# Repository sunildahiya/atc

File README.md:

### Automatic Toilet Cleaner
This repository contains Solidwork design, Navigation Code and IP code for InterIIT Automatic Toilet Cleaner Competition.

#### Minimal HSV Channels for detecting different Color

 1. White    -   Saturation from 0 to someValue
 2. Green    -   Using 1, hue 0 to someValue
 3. Blue     -   saturation from somevalue to 255
 4. Red      -   Using 3, hue from somevalue to 255

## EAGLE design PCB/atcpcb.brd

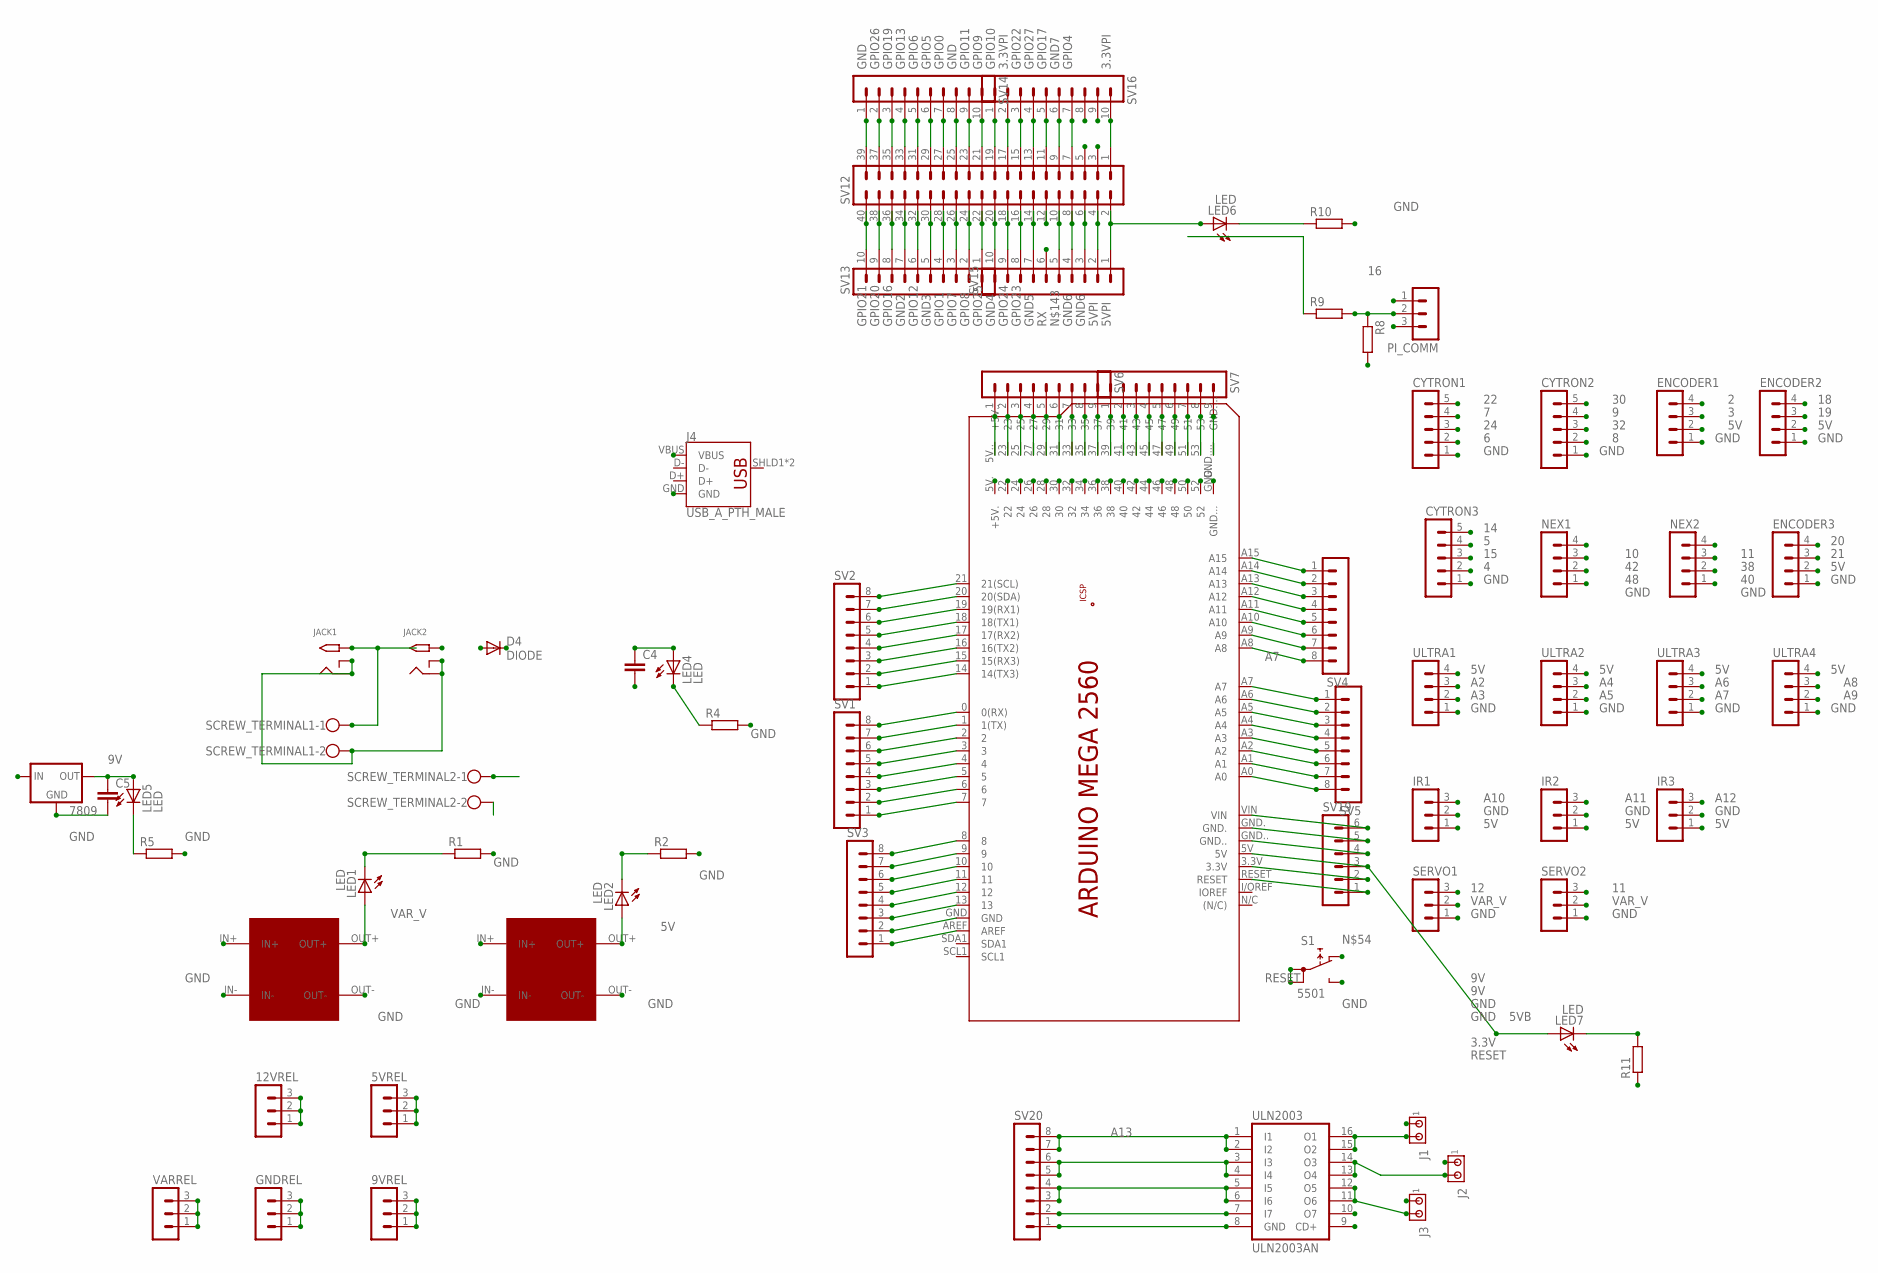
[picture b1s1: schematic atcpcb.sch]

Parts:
5VREL, 9VREL, 12VREL: RELIMATE_03-1; MA03-1
7809: VOLTAGE_REGULATOR_78XXS; 78XXS
C4, C5: CAPACITOR075-063X106; C075-063X106
CYTRON1, CYTRON2, CYTRON3: RELIMATE_05-1; MA05-1
D4: DIODE
ENCODER1, ENCODER2, ENCODER3: RELIMATE_04-1; MA04-1
GNDREL: RELIMATE_03-1; MA03-1
IR1, IR2, IR3: RELIMATE_03-1; MA03-1
J1, J2, J3: MTA02-100; 10X02MTA
J4: USB_A_PTH_MALE; USB-A-H
JACK1, JACK2: 2.1MM_POWER_JACKTHM; POWER_JACK
LED1, LED2, LED4, LED5, LED6, LED7: LED; LED3MM
NEX1, NEX2: RELIMATE_04-1; MA04-1
PCB1: ARDUINO_MEGA2560
PI_COMM: RELIMATE_03-1; MA03-1
R1, R2, R4, R5, R8, R9, R10, R11: RESISTANCE0207/10; 0207/10
S1: 5501
SCREW_TERMINAL1, SCREW_TERMINAL2: SCREW_TERMINAL_POWER; POWER_CONNECTOR
SERVO1, SERVO2: RELIMATE_03-1; MA03-1
SV1, SV2, SV3, SV4, SV5, SV20: RELIMATE_08-1; MA08-1
SV6, SV7: RELIMATE_09-1; MA09-1
SV12: RELIMATE_20-2; MA20-2
SV13, SV14, SV15, SV16: RELIMATE_10-1; MA10-1
SV19: RELIMATE_06-1; MA06-1
U$1, U$2: BUCK_CONVERTER; MPN LNK304DN
ULN2003: ULN2003AN; DIL16
ULTRA1, ULTRA2, ULTRA3, ULTRA4: RELIMATE_04-1; MA04-1
VARREL: RELIMATE_03-1; MA03-1

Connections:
0: PCB1.0 (0(RX)), SV1.8
1: PCB1.1 (1(TX)), SV1.7
2: ENCODER1.4, PCB1.2, SV1.6
3: ENCODER1.3, PCB1.3, SV1.5
3.3V: PCB1.3.3V, SV19.2
3.3VPI: SV12.1, SV12.17, SV16.2, SV16.10
4: CYTRON3.2, PCB1.4, SV1.4
5: CYTRON3.4, PCB1.5, SV1.3
5V: 5VREL.1, 5VREL.2, 5VREL.3, ENCODER1.2, ENCODER2.2, ENCODER3.2, IR1.1, IR2.1, IR3.1, J4.VBUS, LED2.A, U$2.OUT+, ULTRA1.4, ULTRA2.4, ULTRA3.4, ULTRA4.4
5VB: LED7.A, PCB1.5V, SV19.3
5VC: PCB1.5V. (+5V.), PCB1.5V.. (+5V..), SV6.1
5VPI: LED6.A, SV12.2, SV12.4, SV15.1, SV15.2
6: CYTRON1.2, PCB1.6, SV1.2
7: CYTRON1.4, PCB1.7, SV1.1
8: CYTRON2.2, PCB1.8, SV3.8
9: CYTRON2.4, PCB1.9, SV3.7
9V: 9VREL.1, 9VREL.2, 9VREL.3, 7809.OUT, C5.1, LED5.A, PCB1.VIN, SV19.6
10: NEX1.4, PCB1.10, SV3.6
11: NEX2.4, PCB1.11, SERVO2.3, SV3.5
12: PCB1.12, SERVO1.3, SV3.4
12V: 12VREL.1, 12VREL.2, 12VREL.3, 7809.IN, C4.1, D4.C, J1.1, J2.1, J3.1, LED4.A, U$1.IN+, U$2.IN+, ULN2003.9 (CD+)
13: PCB1.13, SV3.3
14: CYTRON3.5, PCB1.14 (14(TX3)), SV2.1
15: CYTRON3.3, PCB1.15 (15(RX3)), SV2.2
16: PCB1.16 (16(TX2)), PI_COMM.1, SV2.3
17: PCB1.17 (17(RX2)), PI_COMM.2, R8.1, R9.2, SV2.4
18: ENCODER2.4, PCB1.18 (18(TX1)), SV2.5
19: ENCODER2.3, PCB1.19 (19(RX1)), SV2.6
20: ENCODER3.4, PCB1.20 (20(SDA)), SV2.7
21: ENCODER3.3, PCB1.21 (21(SCL)), SV2.8
22: CYTRON1.5, PCB1.22
23: PCB1.23, SV6.2
24: CYTRON1.3, PCB1.24
25: PCB1.25, SV6.3
26: PCB1.26
27: PCB1.27, SV6.4
28: PCB1.28
29: PCB1.29, SV6.5
30: CYTRON2.5, PCB1.30
31: PCB1.31, SV6.6
32: CYTRON2.3, PCB1.32
33: PCB1.33, SV6.7
34: PCB1.34
35: PCB1.35, SV6.8
36: PCB1.36
37: PCB1.37, SV6.9
38: NEX2.3, PCB1.38
39: PCB1.39, SV7.1
40: NEX2.2, PCB1.40
41: PCB1.41, SV7.2
42: NEX1.3, PCB1.42
43: PCB1.43, SV7.3
44: PCB1.44
45: PCB1.45, SV7.4
46: PCB1.46
47: PCB1.47, SV7.5
48: NEX1.2, PCB1.48
49: PCB1.49, SV7.6
50: PCB1.50
51: PCB1.51, SV7.7
52: PCB1.52
53: PCB1.53, SV7.8
A0: PCB1.A0, SV5.8
A1: PCB1.A1, SV5.7
A2: PCB1.A2, SV5.6, ULTRA1.3
A3: PCB1.A3, SV5.5, ULTRA1.2
A4: PCB1.A4, SV5.4, ULTRA2.3
A5: PCB1.A5, SV5.3, ULTRA2.2
A6: PCB1.A6, SV5.2, ULTRA3.3
A7: PCB1.A7, SV5.1, ULTRA3.2
A8: PCB1.A8, SV4.8, ULTRA4.3
A9: PCB1.A9, SV4.7, ULTRA4.2
A10: IR1.3, PCB1.A10, SV4.6
A11: IR2.3, PCB1.A11, SV4.5
A12: IR3.3, PCB1.A12, SV4.4
A13: PCB1.A13, SV4.3, SV20.7, SV20.8, ULN2003.1 (I1), ULN2003.2 (I2)
A14: PCB1.A14, SV4.2, SV20.5, SV20.6, ULN2003.3 (I3), ULN2003.4 (I4)
A15: PCB1.A15, SV4.1, SV20.3, SV20.4, ULN2003.5 (I5), ULN2003.6 (I6)
AREF: PCB1.AREF, SV3.1
GND: 7809.GND, C4.2, C5.2, CYTRON1.1, CYTRON2.1, CYTRON3.1, ENCODER1.1, ENCODER2.1, ENCODER3.1, GNDREL.1, GNDREL.2, GNDREL.3, IR1.2, IR2.2, IR3.2, J4.GND, JACK1.RING, JACK1.RING_SW, JACK2.RING, JACK2.RING_SW, NEX1.1, NEX2.1, PCB1.GND, PCB1.GND., PCB1.GND.., PCB1.GND..., PCB1.GND...., PI_COMM.3, R1.2, R2.2, R4.2, R5.2, R8.2, R10.2, R11.1, S1.NO, SCREW_TERMINAL1.2, SCREW_TERMINAL2.2, SERVO1.1, SERVO2.1, SV3.2, SV7.9, SV12.25, SV12.39, SV14.1, SV14.8, SV19.4, SV19.5, SV20.1, U$1.IN-, U$1.OUT-, U$2.IN-, U$2.OUT-, ULN2003.8 (GND), ULTRA1.1, ULTRA2.1, ULTRA3.1, ULTRA4.1
GND2: SV12.34, SV13.7
GND3: SV12.30, SV13.5
GND4: SV12.20, SV15.10
GND5: SV12.14, SV15.7
GND6: SV12.6, SV12.8, SV15.3, SV15.4
GND7: SV12.9, SV16.6
GPIO0: SV12.27, SV14.7
GPIO1: SV12.28, SV13.4
GPIO4: SV12.7, SV16.7
GPIO5: SV12.29, SV14.6
GPIO6: SV12.31, SV14.5
GPIO7: SV12.26, SV13.3
GPIO8: SV12.24, SV13.2
GPIO9: SV12.21, SV14.10
GPIO10: SV12.19, SV16.1
GPIO11: SV12.23, SV14.9
GPIO12: SV12.32, SV13.6
GPIO13: SV12.33, SV14.4
GPIO16: SV12.36, SV13.8
GPIO17: SV12.11, SV16.5
GPIO19: SV12.35, SV14.3
GPIO20: SV12.38, SV13.9
GPIO21: SV12.40, SV13.10
GPIO22: SV12.15, SV16.3
GPIO23: SV12.16, SV15.8
GPIO24: SV12.18, SV15.9
GPIO25: SV12.22, SV13.1
GPIO26: SV12.37, SV14.2
GPIO27: SV12.13, SV16.4
unnamed: LED1.K (C), R1.1
unnamed: LED2.K (C), R2.1
unnamed: LED6.K (C), R10.1
unnamed: LED7.K (C), R11.2
unnamed: SV20.2, ULN2003.7 (I7)
unnamed: J1.2, ULN2003.15 (O2), ULN2003.16 (O1)
unnamed: J2.2, ULN2003.13 (O4), ULN2003.14 (O3)
unnamed: J3.2, ULN2003.11 (O6), ULN2003.12 (O5)
unnamed: LED4.K (C), R4.1
unnamed: LED5.K (C), R5.1
unnamed: SV12.10, SV15.5
RESET: PCB1.RESET, S1.1A, S1.1B, SV19.1
RX: R9.1, SV12.12, SV15.6
SCL: SV12.5, SV16.8
SDA: SV12.3, SV16.9
VAR_V: LED1.A, SERVO1.2, SERVO2.2, U$1.OUT+, VARREL.1, VARREL.2, VARREL.3
VIN: D4.A, JACK1.TIP, JACK2.TIP, SCREW_TERMINAL1.1, SCREW_TERMINAL2.1

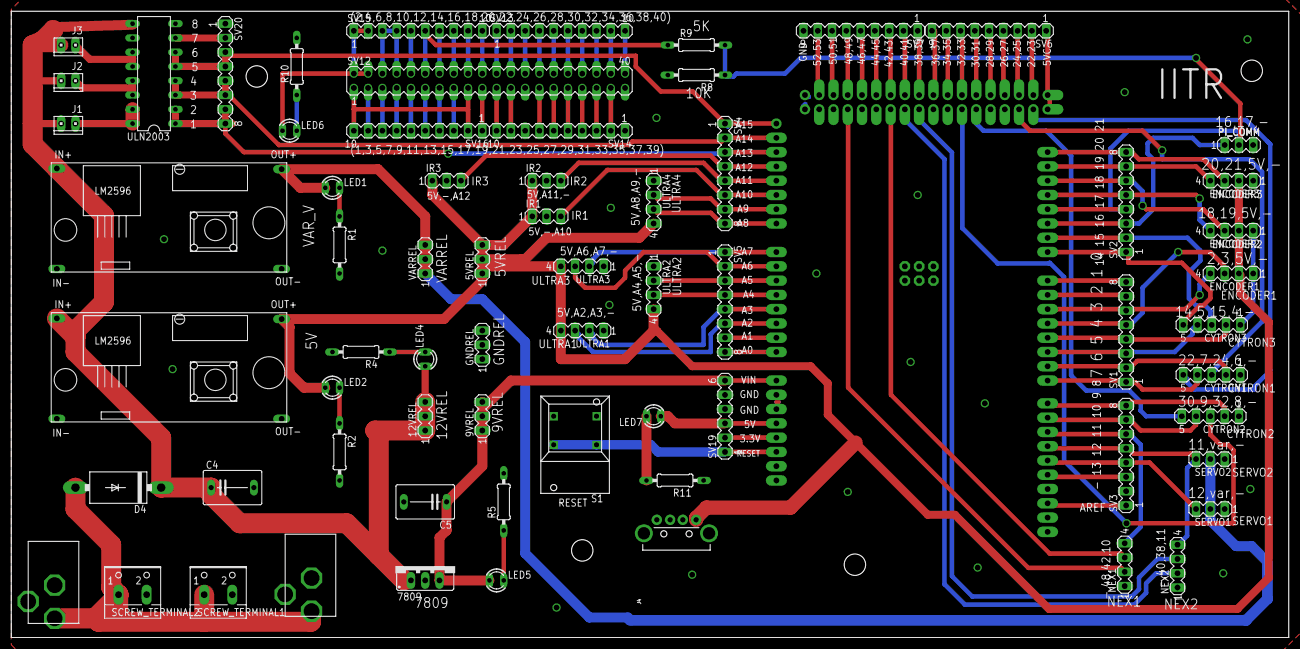
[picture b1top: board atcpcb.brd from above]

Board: 2 copper layers, 227.3 x 111.4 mm, 68 parts (1 on the bottom side), 118 nets.

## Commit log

2017-12-06 Code is added to calculate bot position using encoder
2017-12-16 Fixed issues and added code to navigate bot using encoders in straight line
2017-12-16 Added PCB eagle design
2017-12-21 Fixed some syntax issues and tune pid parameter
2017-12-24 Added code to navigate bot in straight line using ultrasonic sensor
2017-12-25 Added code for reading front ultrasonic sensor and fixes issues
2017-12-25 Fix backward direction correction issue and tune PID parameters
2017-12-26 Added code to navigate bot in straight line using front ultrasonic for angle and left ultrasonic for shift correction
2017-12-26 Added code to rotate bot by 90 degree and allign itself to left sensors
2017-12-27 Added code to clean stage 1 but need some fixes
2017-12-27 Added code for commode mechanism. IR need to be incorporated
2017-12-28 Added code for stage 2(commode) cleaning
2017-12-28 Added code for calculating world co-ordinates w.r.t. bottom-left corner
2017-12-28 Added code for testing ptrans module
2017-12-30 Code is added to read IMU
2017-12-30 Serial print util functions are added
2017-12-31 Code is added for stage 3 upto commode
2017-12-31 Tune Parameters
2018-01-01 Navigation motor driver is changed
2018-01-01 Code is added to clean upto commode
2018-01-02 Code is added to clean upto stage 4
2018-01-02 Added code for reading MPU9050
2018-01-02 Added Entry1 complete code
2018-01-06 Code is added for all entrance
2018-01-06 Added Point class
2018-01-06 Blob class and blobs extraction function from black and white image is added
2018-01-06 Code is added for stain detection
2018-01-06 Some helper function are added
2018-01-06 Main file is added
2018-01-06 Redundant code is removed form blob and merge_blob file
2018-01-06 Some more code is added to test_modules
2018-01-06 Modified Code
2018-01-06 Modified for custom arena
2018-01-07 Almost Final
2018-01-09 Failure
2018-01-09 Added images for testing algorithm
2018-01-09 Added old and unused code
2018-01-12 Added code for serial communication via arduino cable between arduino and raspberry pi
2018-01-12 Untested code file for "pi" is added
2018-02-13 Modify gitignore file to exclude Mechanical dir
2018-02-13 Add final bot solidworks design
2018-08-01 Add: README

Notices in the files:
parts and their libraries:
SparkFun-Connectors: Licensing: Creative Commons ShareAlike 4.0 International - https://creativecommons.org/licenses/by-sa/4.0
